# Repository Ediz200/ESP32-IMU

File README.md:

# ESP32-IMU
 ESP32 based PCB interfacing with the BMI088

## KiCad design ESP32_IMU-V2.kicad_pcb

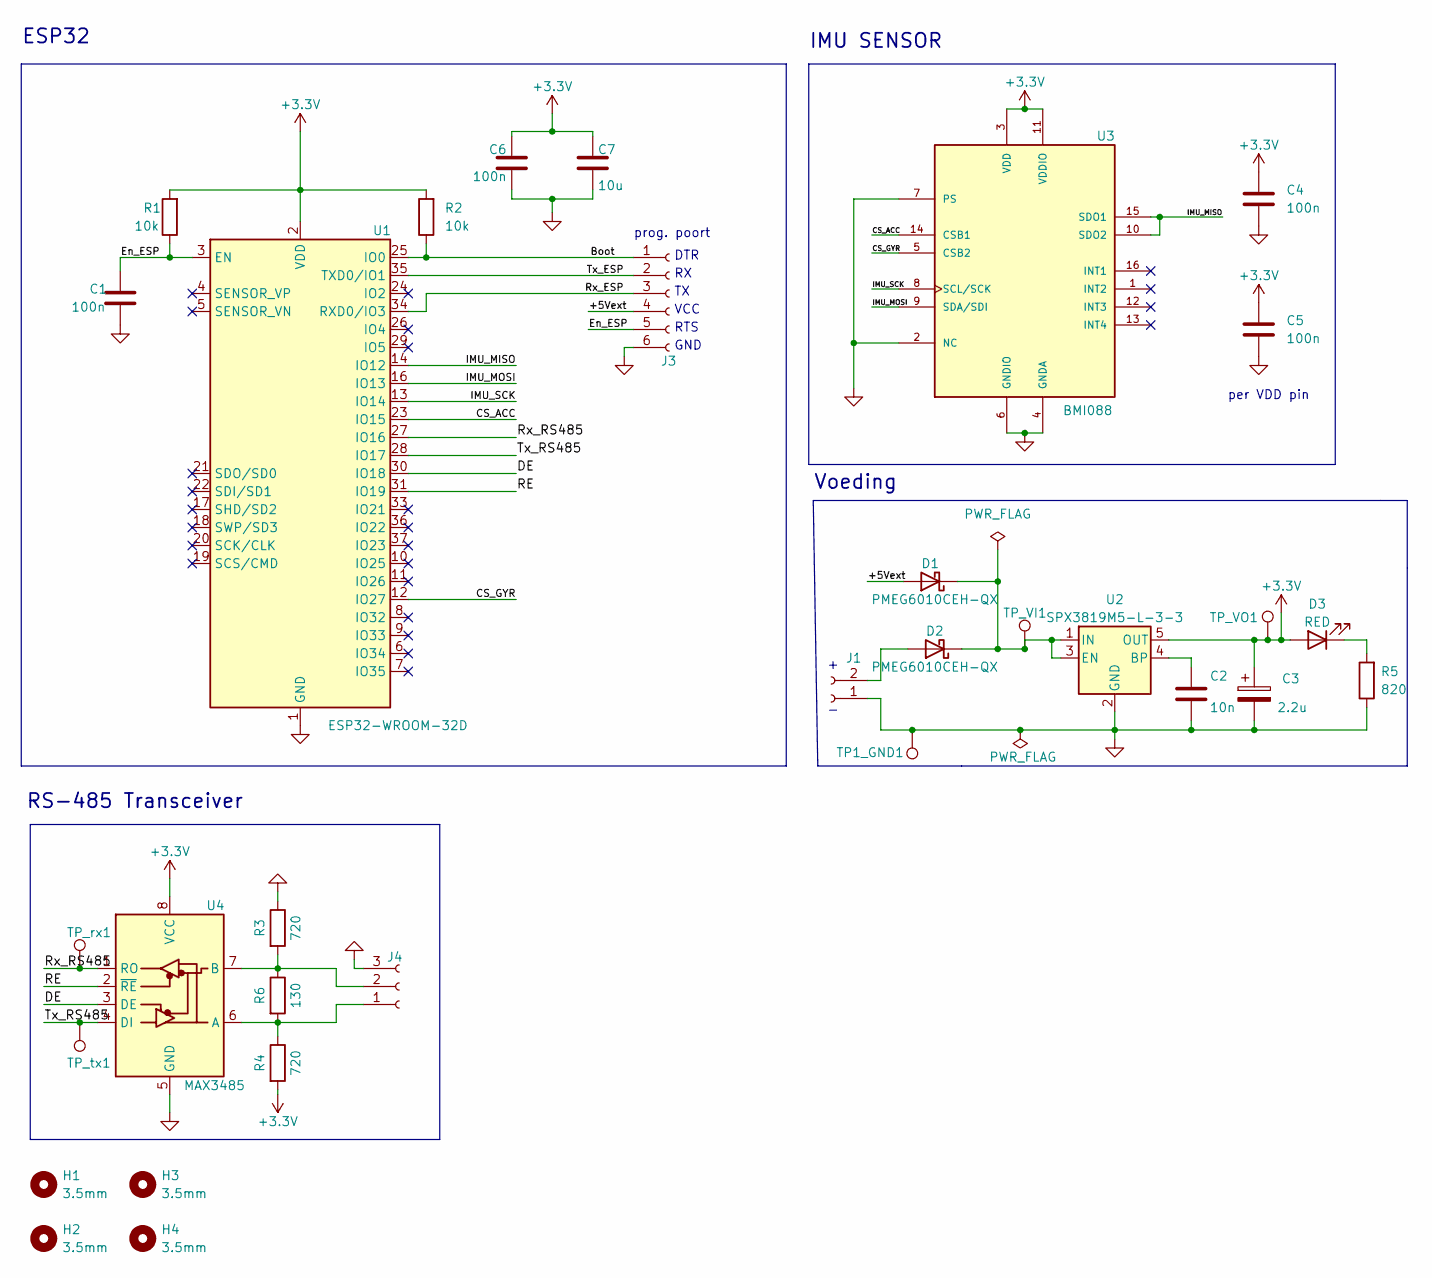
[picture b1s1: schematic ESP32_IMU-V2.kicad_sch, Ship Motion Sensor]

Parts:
C1, C4, C5, C6: 100n; C_0805_2012Metric_Pad1.18x1.45mm_HandSolder
C2: 10n; C_0805_2012Metric_Pad1.18x1.45mm_HandSolder
C3: 2.2u; CP_Elec_4x3.9
C7: 10u; C_0805_2012Metric_Pad1.18x1.45mm_HandSolder
D1, D2: PMEG6010CEH-QX; D_SOD-123F
D3: RED; LED_1206_3216Metric_Pad1.42x1.75mm_HandSolder
H1, H2, H3, H4: 3.5mm; MountingHole_3.5mm
J1: Conn_01x02_Female; PhoenixContact_MC_1,5_2-G-3.81_1x02_P3.81mm_Horizontal
J3: Conn_01x06_Female; PinSocket_1x06_P2.54mm_Vertical
J4: Conn_01x03_Female; PhoenixContact_MC_1,5_3-G-3.81_1x03_P3.81mm_Horizontal
R1, R2: 10k; R_0805_2012Metric_Pad1.20x1.40mm_HandSolder
R3, R4: 720; R_0805_2012Metric_Pad1.20x1.40mm_HandSolder
R5: 820; R_0805_2012Metric_Pad1.20x1.40mm_HandSolder
R6: 130; R_0805_2012Metric_Pad1.20x1.40mm_HandSolder
TP1_GND1: TestPoint; TestPoint_THTPad_1.5x1.5mm_Drill0.7mm
TP_VI1: TestPoint; TestPoint_THTPad_1.5x1.5mm_Drill0.7mm
TP_VO1: TestPoint; TestPoint_THTPad_1.5x1.5mm_Drill0.7mm
TP_rx1: TestPoint; TestPoint_THTPad_1.5x1.5mm_Drill0.7mm
TP_tx1: TestPoint; TestPoint_THTPad_1.5x1.5mm_Drill0.7mm
U1: ESP32-WROOM-32D; ESP32-WROOM-32
U2: SPX3819M5-L-3-3; SOT-23-5
U3: BMI088; LGA_16_cw
U4: MAX3485; SOIC-8_3.9x4.9mm_P1.27mm

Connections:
+3V3: C3.1, C4.1, C5.1, C6.2, C7.1, D3.2 (A), R1.2, R2.2, R4.2, TP_VO1.1, U1.2 (VDD), U2.5 (OUT), U3.3 (VDD), U3.11 (VDDIO), U4.8 (VCC)
/+5Vext: D1.2 (A), J3.4
/Boot: J3.1, R2.1, U1.25 (IO0)
/CS_ACC: U1.23 (IO15), U3.14 (CSB1)
/CS_GYR: U1.12 (IO27), U3.5 (CSB2)
/DE: U1.30 (IO18), U4.3 (DE)
/En_ESP: C1.1, J3.5, R1.1, U1.3 (EN)
/IMU_MISO: U1.14 (IO12), U3.10 (SDO2), U3.15 (SDO1)
/IMU_MOSI: U1.16 (IO13), U3.9 (SDA/SDI)
/IMU_SCK: U1.13 (IO14), U3.8 (SCL/SCK)
/RE: U1.31 (IO19), U4.2 (~RE)
/Rx_ESP: J3.3, U1.34 (RXD0/IO3)
/Rx_RS485: TP_rx1.1, U1.27 (IO16), U4.1 (RO)
/Tx_ESP: J3.2, U1.35 (TXD0/IO1)
/Tx_RS485: TP_tx1.1, U1.28 (IO17), U4.4 (DI)
GND: C1.2, C2.2, C3.2, C4.2, C5.2, C6.1, C7.2, J1.1, J3.6, J4.3, R3.1, R5.1, TP1_GND1.1, U1.1 (GND), U1.15 (GND), U1.38 (GND), U1.39 (GND), U2.2 (GND), U3.2 (NC), U3.4 (GNDA), U3.6 (GNDIO), U3.7 (PS), U4.5 (GND)
unnamed: C2.1, U2.4 (BP)
unnamed: D1.1 (K), D2.1 (K), TP_VI1.1, U2.1 (IN), U2.3 (EN)
unnamed: D2.2 (A), J1.2
unnamed: D3.1 (K), R5.2
unnamed: J4.1, R4.1, R6.2, U4.6 (A)
unnamed: J4.2, R3.2, R6.1, U4.7 (B)

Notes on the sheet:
GND
RS-485 Transceiver
ESP32
prog. poort
per VDD pin
DTR
Voeding
IMU SENSOR
RTS
VCC

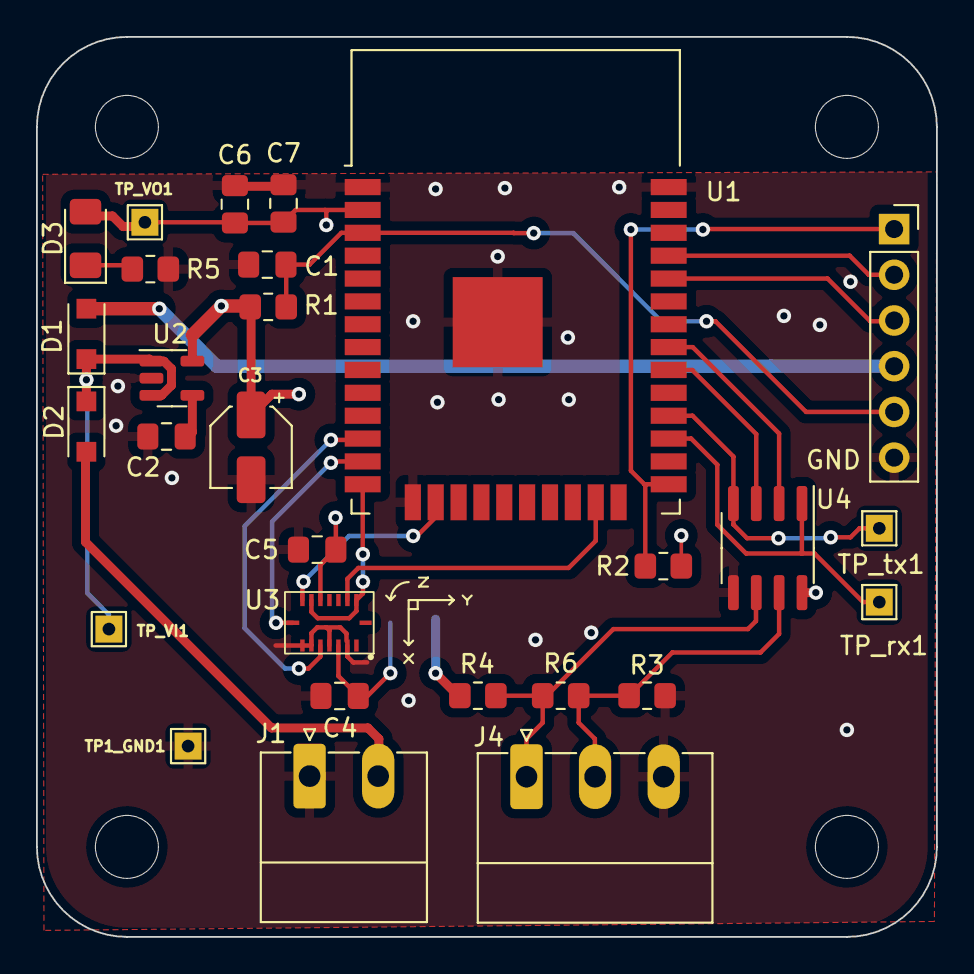
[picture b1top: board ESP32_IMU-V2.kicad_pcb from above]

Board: 2 copper layers, 50.0 x 50.0 mm, 32 parts (0 on the bottom side), 22 nets.

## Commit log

2023-03-02 test
2023-03-03 finale version
2023-03-08 Update sens2sea_imu.ino
    RS_485 pinnen hoog gemaakt.
